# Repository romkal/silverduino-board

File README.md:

# silverduino-board

This is eagle project with a shield for silverduino.

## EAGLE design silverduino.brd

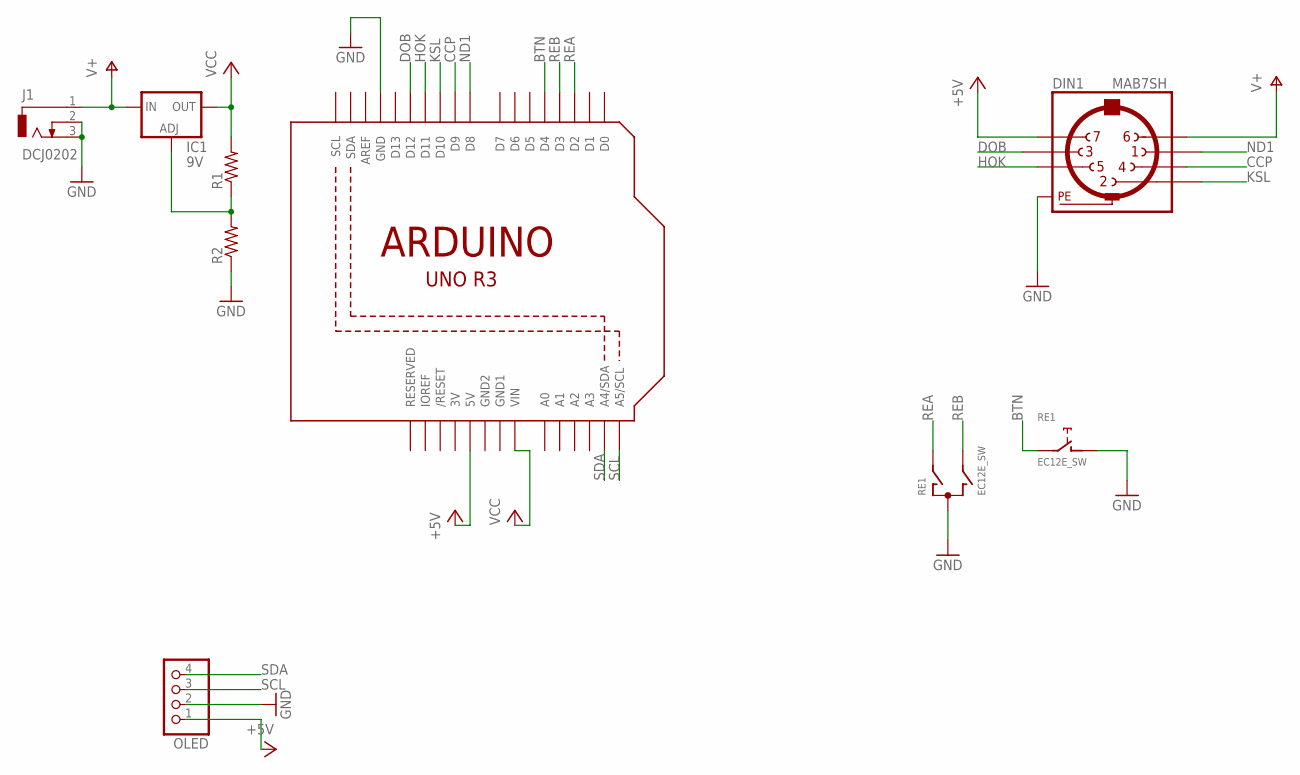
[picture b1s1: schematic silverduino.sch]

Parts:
DIN1: MAB7SH
IC1: 9V; 317TL
J1: DCJ0202
OLED: PINHD-1X4; 1X04
R1, R2: R-US_0207/10; 0207/10
RE1: EC12E_SW; ALPS_EC12E_SW
U1: ARDUINOR3-DIMENSION; ARDUINOR3

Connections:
3V: U1.3V
+5V: DIN1.7, OLED.1, U1.5V
BTN: RE1.E (2), U1.D4
CCP: DIN1.4, U1.D9
DOB: DIN1.3, U1.D12
GND: DIN1.PE, DIN1.PE@ (PE), J1.2, J1.3, OLED.2, R2.1, RE1.C, RE1.D (1), U1.GND
GND1: U1.GND1
GND2: U1.GND2
HOK: DIN1.5, U1.D11
KSL: DIN1.2, U1.D10
unnamed: IC1.1 (ADJ), R1.1, R2.2
ND1: DIN1.1, U1.D8
REA: RE1.A, U1.D2
REB: RE1.B, U1.D3
SCL: OLED.3, U1.A5 (A5/SCL)
SDA: OLED.4, U1.A4 (A4/SDA)
V+: DIN1.6, IC1.3 (IN), J1.1
VCC: IC1.2 (OUT), R1.2, U1.VIN

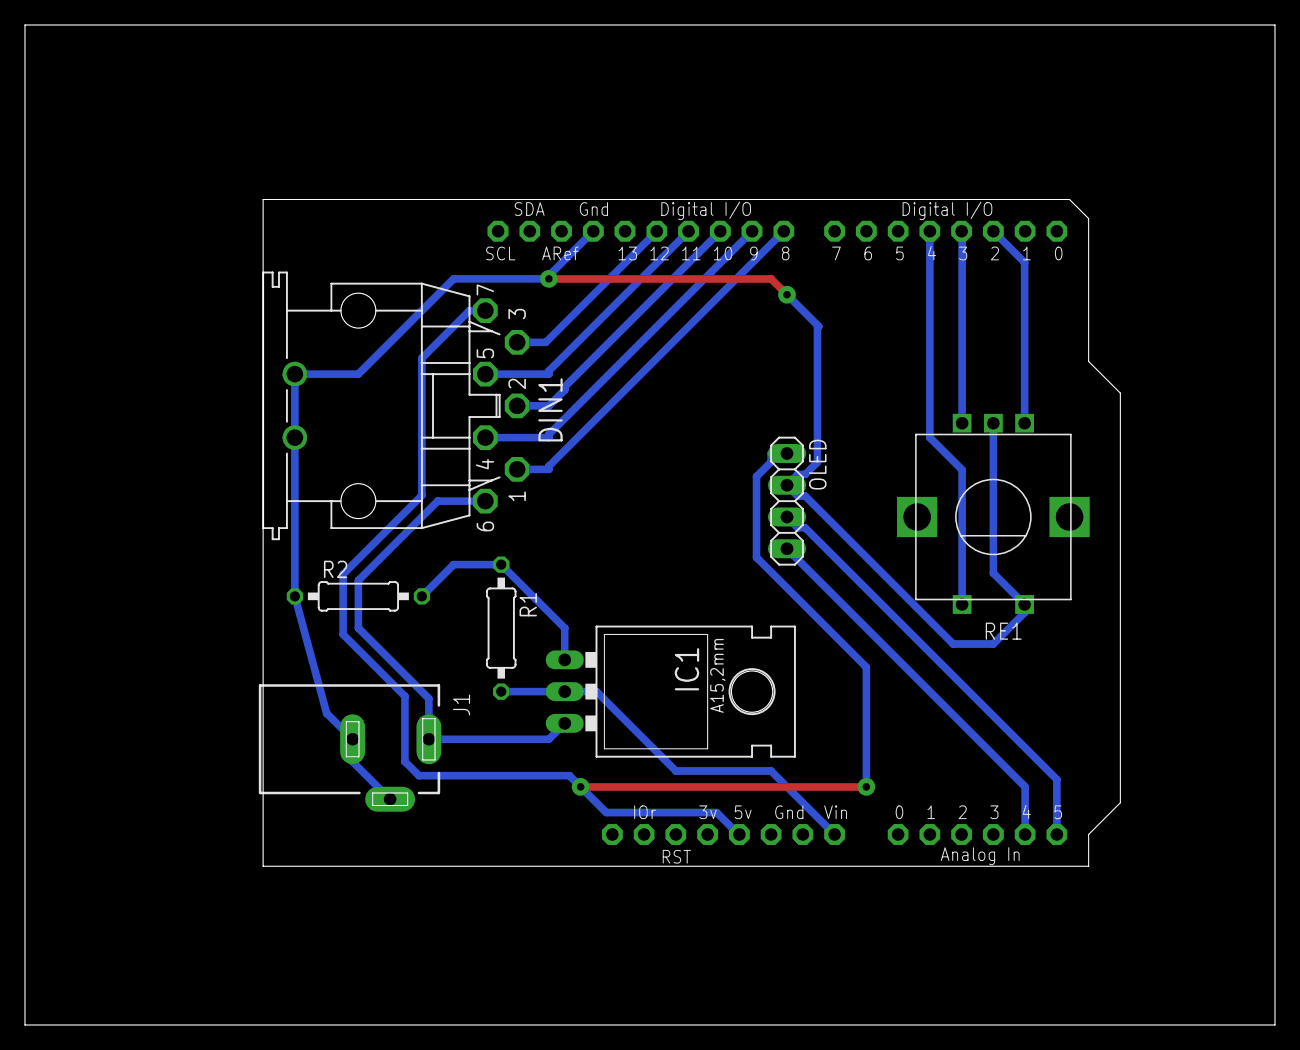
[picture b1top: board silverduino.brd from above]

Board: 2 copper layers, 100.0 x 80.0 mm, 8 parts (0 on the bottom side), 15 nets.

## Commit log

2017-03-17 Board
2017-07-28 Added openscad and kicad projects.
